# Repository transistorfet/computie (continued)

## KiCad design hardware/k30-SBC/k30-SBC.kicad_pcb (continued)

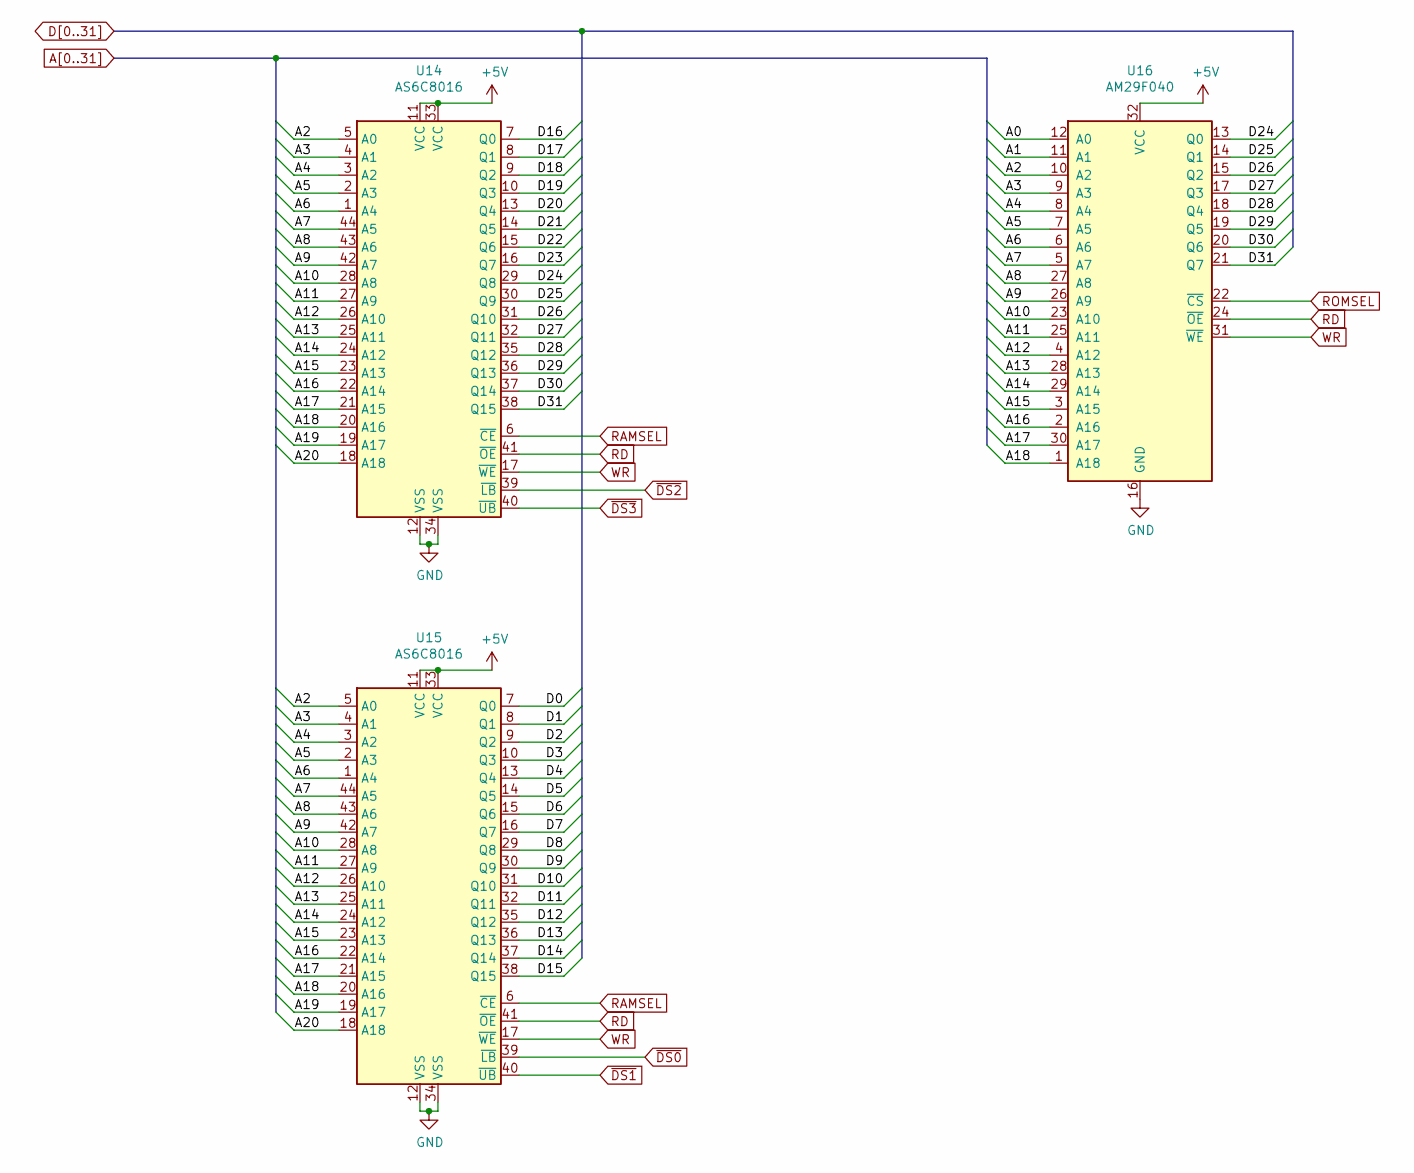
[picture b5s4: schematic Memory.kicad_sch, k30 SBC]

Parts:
U14, U15: AS6C8016; TSOP-II-44_10.16x18.41mm_P0.8mm
U16: AM29F040; PLCC-32_THT-Socket

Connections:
+5V: U14.11 (VCC), U14.33 (VCC), U15.11 (VCC), U15.33 (VCC), U16.32 (VCC); also elsewhere on the board
A0: U16.12 (A0); also elsewhere on the board
A1: U16.11 (A1); also elsewhere on the board
A2: U14.5 (A0), U15.5 (A0), U16.10 (A2); also elsewhere on the board
A3: U14.4 (A1), U15.4 (A1), U16.9 (A3); also elsewhere on the board
A4: U14.3 (A2), U15.3 (A2), U16.8 (A4); also elsewhere on the board
A5: U14.2 (A3), U15.2 (A3), U16.7 (A5); also elsewhere on the board
A6: U14.1 (A4), U15.1 (A4), U16.6 (A6); also elsewhere on the board
A7: U14.44 (A5), U15.44 (A5), U16.5 (A7); also elsewhere on the board
A8: U14.43 (A6), U15.43 (A6), U16.27 (A8); also elsewhere on the board
A9: U14.42 (A7), U15.42 (A7), U16.26 (A9); also elsewhere on the board
A10: U14.28 (A8), U15.28 (A8), U16.23 (A10); also elsewhere on the board
A11: U14.27 (A9), U15.27 (A9), U16.25 (A11); also elsewhere on the board
A12: U14.26 (A10), U15.26 (A10), U16.4 (A12); also elsewhere on the board
A13: U14.25 (A11), U15.25 (A11), U16.28 (A13); also elsewhere on the board
A14: U14.24 (A12), U15.24 (A12), U16.29 (A14); also elsewhere on the board
A15: U14.23 (A13), U15.23 (A13), U16.3 (A15); also elsewhere on the board
A16: U14.22 (A14), U15.22 (A14), U16.2 (A16); also elsewhere on the board
A17: U14.21 (A15), U15.21 (A15), U16.30 (A17); also elsewhere on the board
A18: U14.20 (A16), U15.20 (A16), U16.1 (A18); also elsewhere on the board
A19: U14.19 (A17), U15.19 (A17); also elsewhere on the board
A20: U14.18 (A18), U15.18 (A18); also elsewhere on the board
D0: U15.7 (Q0); also elsewhere on the board
D1: U15.8 (Q1); also elsewhere on the board
D2: U15.9 (Q2); also elsewhere on the board
D3: U15.10 (Q3); also elsewhere on the board
D4: U15.13 (Q4); also elsewhere on the board
D5: U15.14 (Q5); also elsewhere on the board
D6: U15.15 (Q6); also elsewhere on the board
D7: U15.16 (Q7); also elsewhere on the board
D8: U15.29 (Q8); also elsewhere on the board
D9: U15.30 (Q9); also elsewhere on the board
D10: U15.31 (Q10); also elsewhere on the board
D11: U15.32 (Q11); also elsewhere on the board
D12: U15.35 (Q12); also elsewhere on the board
D13: U15.36 (Q13); also elsewhere on the board
D14: U15.37 (Q14); also elsewhere on the board
D15: U15.38 (Q15); also elsewhere on the board
D16: U14.7 (Q0); also elsewhere on the board
D17: U14.8 (Q1); also elsewhere on the board
D18: U14.9 (Q2); also elsewhere on the board
D19: U14.10 (Q3); also elsewhere on the board
D20: U14.13 (Q4); also elsewhere on the board
D21: U14.14 (Q5); also elsewhere on the board
D22: U14.15 (Q6); also elsewhere on the board
D23: U14.16 (Q7); also elsewhere on the board
D24: U14.29 (Q8), U16.13 (Q0); also elsewhere on the board
D25: U14.30 (Q9), U16.14 (Q1); also elsewhere on the board
D26: U14.31 (Q10), U16.15 (Q2); also elsewhere on the board
D27: U14.32 (Q11), U16.17 (Q3); also elsewhere on the board
D28: U14.35 (Q12), U16.18 (Q4); also elsewhere on the board
D29: U14.36 (Q13), U16.19 (Q5); also elsewhere on the board
D30: U14.37 (Q14), U16.20 (Q6); also elsewhere on the board
D31: U14.38 (Q15), U16.21 (Q7); also elsewhere on the board
GND: U14.12 (VSS), U14.34 (VSS), U15.12 (VSS), U15.34 (VSS), U16.16 (GND); also elsewhere on the board
RAMSEL: U14.6 (~CE), U15.6 (~CE); also elsewhere on the board
RD: U14.41 (~OE), U15.41 (~OE), U16.24 (~OE); also elsewhere on the board
ROMSEL: U16.22 (~CS); also elsewhere on the board
WR: U14.17 (~WE), U15.17 (~WE), U16.31 (~WE); also elsewhere on the board
~DS0: U15.39 (~LB); also elsewhere on the board
~DS1: U15.40 (~UB); also elsewhere on the board
~DS2: U14.39 (~LB); also elsewhere on the board
~DS3: U14.40 (~UB); also elsewhere on the board

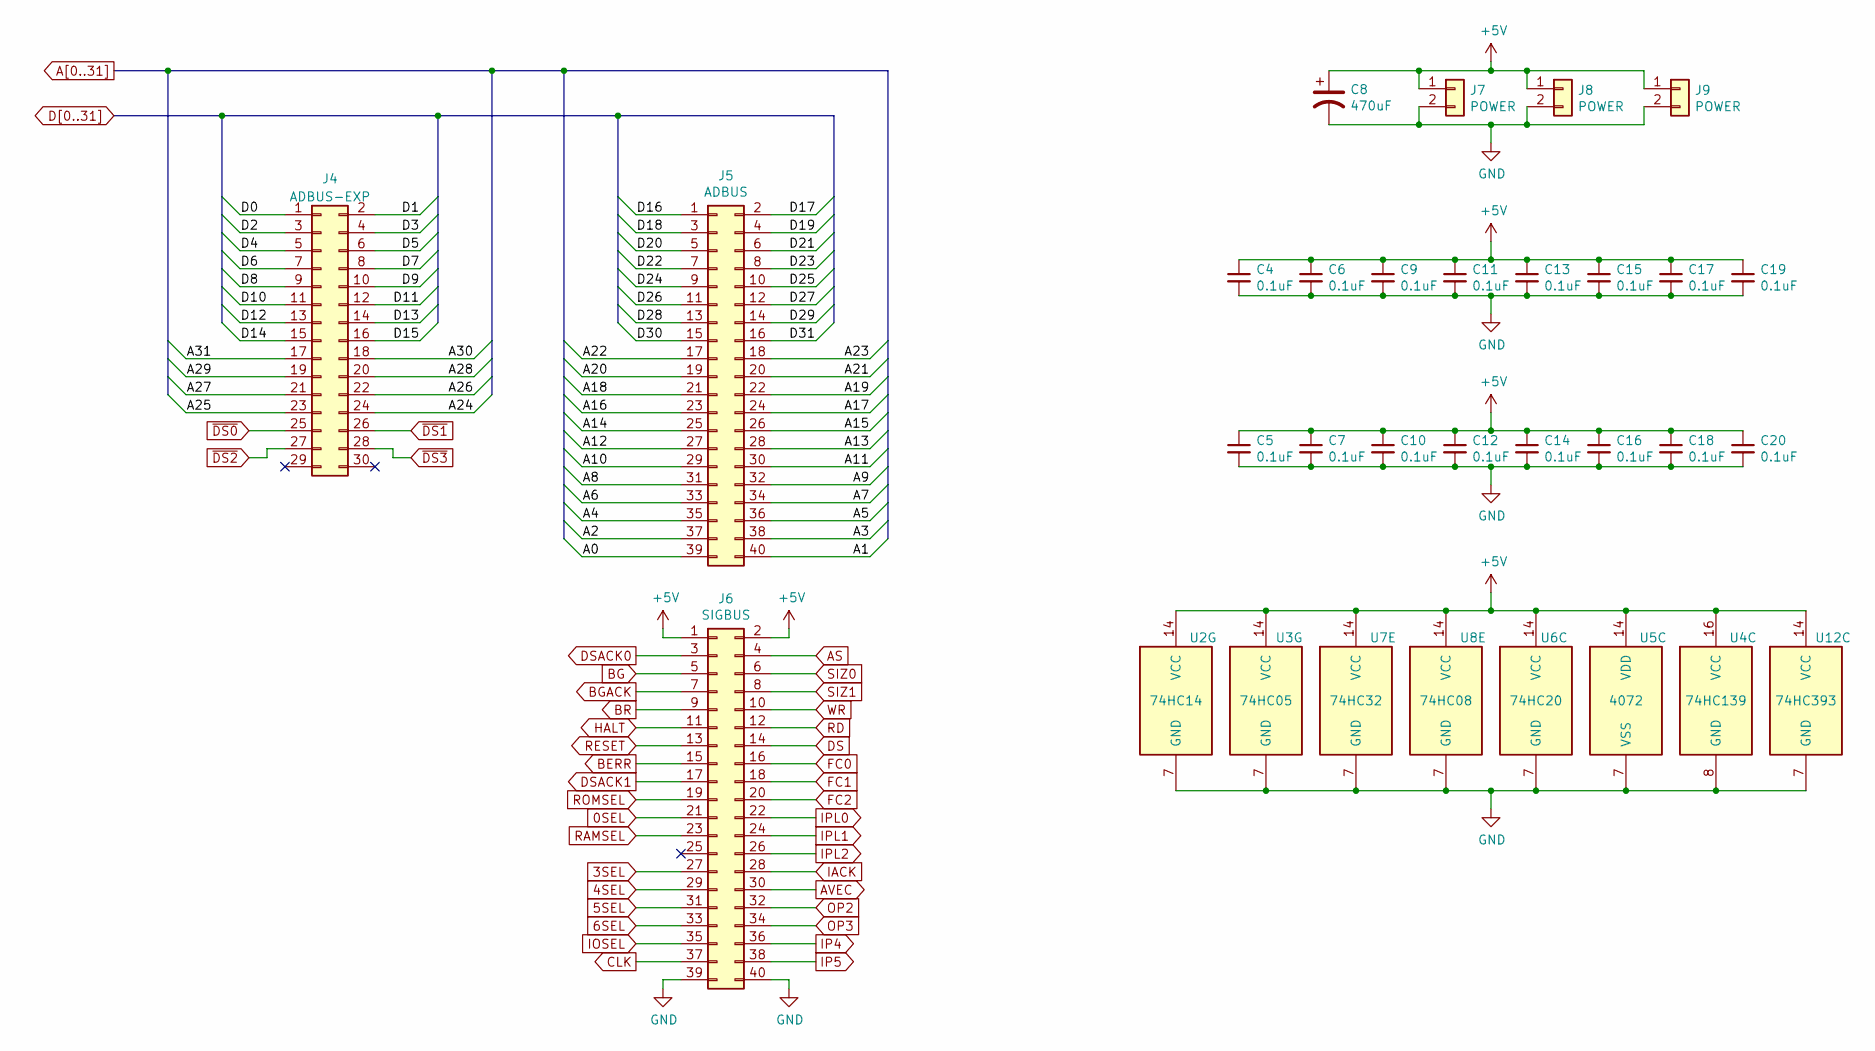
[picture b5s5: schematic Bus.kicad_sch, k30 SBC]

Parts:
C4, C5, C6, C7, C9, C10, C11, C12, C13, C14, C15, C16, C17, C18, C19, C20: 0.1uF; C_Disc_D3.0mm_W2.0mm_P2.50mm
C8: 470uF; CP_Radial_D8.0mm_P5.00mm
J4: ADBUS-EXP; PinHeader_2x15_P2.54mm_Vertical
J5: ADBUS; PinHeader_2x20_P2.54mm_Vertical
J6: SIGBUS; PinHeader_2x20_P2.54mm_Vertical
J7, J8, J9: POWER; PinHeader_1x02_P2.54mm_Vertical
U2: 74HC14; TSSOP-14_4.4x5mm_P0.65mm
U3: 74HC05; TSSOP-14_4.4x5mm_P0.65mm
U4: 74HC139; TSSOP-16_4.4x5mm_P0.65mm
U5: 4072; TSSOP-14_4.4x5mm_P0.65mm
U6: 74HC20; TSSOP-14_4.4x5mm_P0.65mm
U7: 74HC32; TSSOP-14_4.4x5mm_P0.65mm
U8: 74HC08; TSSOP-14_4.4x5mm_P0.65mm
U12: 74HC393; TSSOP-14_4.4x5mm_P0.65mm

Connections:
0SEL: J6.21; also elsewhere on the board
3SEL: J6.27; also elsewhere on the board
4SEL: J6.29; also elsewhere on the board
5SEL: J6.31; also elsewhere on the board
6SEL: J6.33; also elsewhere on the board
+5V: C4.1, C5.1, C6.1, C7.1, C8.1, C9.1, C10.1, C11.1, C12.1, C13.1, C14.1, C15.1, C16.1, C17.1, C18.1, C19.1, C20.1, J6.1, J6.2, J7.1, J8.1, J9.1, U2.14 (VCC), U3.14 (VCC), U4.16 (VCC), U5.14 (VDD), U6.14 (VCC), U7.14 (VCC), U8.14 (VCC), U12.14 (VCC); also elsewhere on the board
A0: J5.39; also elsewhere on the board
A1: J5.40; also elsewhere on the board
A2: J5.37; also elsewhere on the board
A3: J5.38; also elsewhere on the board
A4: J5.35; also elsewhere on the board
A5: J5.36; also elsewhere on the board
A6: J5.33; also elsewhere on the board
A7: J5.34; also elsewhere on the board
A8: J5.31; also elsewhere on the board
A9: J5.32; also elsewhere on the board
A10: J5.29; also elsewhere on the board
A11: J5.30; also elsewhere on the board
A12: J5.27; also elsewhere on the board
A13: J5.28; also elsewhere on the board
A14: J5.25; also elsewhere on the board
A15: J5.26; also elsewhere on the board
A16: J5.23; also elsewhere on the board
A17: J5.24; also elsewhere on the board
A18: J5.21; also elsewhere on the board
A19: J5.22; also elsewhere on the board
A20: J5.19; also elsewhere on the board
A21: J5.20; also elsewhere on the board
A22: J5.17; also elsewhere on the board
A23: J5.18; also elsewhere on the board
A24: J4.24; also elsewhere on the board
A25: J4.23; also elsewhere on the board
A26: J4.22; also elsewhere on the board
A27: J4.21; also elsewhere on the board
A28: J4.20; also elsewhere on the board
A29: J4.19; also elsewhere on the board
A30: J4.18; also elsewhere on the board
A31: J4.17; also elsewhere on the board
AS: J6.4; also elsewhere on the board
AVEC: J6.30; also elsewhere on the board
BERR: J6.15; also elsewhere on the board
BG: J6.5; also elsewhere on the board
BGACK: J6.7; also elsewhere on the board
BR: J6.9; also elsewhere on the board
CLK: J6.37; also elsewhere on the board
D0: J4.1; also elsewhere on the board
D1: J4.2; also elsewhere on the board
D2: J4.3; also elsewhere on the board
D3: J4.4; also elsewhere on the board
D4: J4.5; also elsewhere on the board
D5: J4.6; also elsewhere on the board
D6: J4.7; also elsewhere on the board
D7: J4.8; also elsewhere on the board
D8: J4.9; also elsewhere on the board
D9: J4.10; also elsewhere on the board
D10: J4.11; also elsewhere on the board
D11: J4.12; also elsewhere on the board
D12: J4.13; also elsewhere on the board
D13: J4.14; also elsewhere on the board
D14: J4.15; also elsewhere on the board
D15: J4.16; also elsewhere on the board
D16: J5.1; also elsewhere on the board
D17: J5.2; also elsewhere on the board
D18: J5.3; also elsewhere on the board
D19: J5.4; also elsewhere on the board
D20: J5.5; also elsewhere on the board
D21: J5.6; also elsewhere on the board
D22: J5.7; also elsewhere on the board
D23: J5.8; also elsewhere on the board
D24: J5.9; also elsewhere on the board
D25: J5.10; also elsewhere on the board
D26: J5.11; also elsewhere on the board
D27: J5.12; also elsewhere on the board
D28: J5.13; also elsewhere on the board
D29: J5.14; also elsewhere on the board
D30: J5.15; also elsewhere on the board
D31: J5.16; also elsewhere on the board
DS: J6.14; also elsewhere on the board
DSACK0: J6.3; also elsewhere on the board
DSACK1: J6.17; also elsewhere on the board
FC0: J6.16; also elsewhere on the board
FC1: J6.18; also elsewhere on the board
FC2: J6.20; also elsewhere on the board
GND: C4.2, C5.2, C6.2, C7.2, C8.2, C9.2, C10.2, C11.2, C12.2, C13.2, C14.2, C15.2, C16.2, C17.2, C18.2, C19.2, C20.2, J6.39, J6.40, J7.2, J8.2, J9.2, U2.7 (GND), U3.7 (GND), U4.8 (GND), U5.7 (VSS), U6.7 (GND), U7.7 (GND), U8.7 (GND), U12.7 (GND); also elsewhere on the board
HALT: J6.11; also elsewhere on the board
IACK: J6.28; also elsewhere on the board
IOSEL: J6.35; also elsewhere on the board
IP4: J6.36; also elsewhere on the board
IP5: J6.38; also elsewhere on the board
IPL0: J6.22; also elsewhere on the board
IPL1: J6.24; also elsewhere on the board
IPL2: J6.26; also elsewhere on the board
OP2: J6.32; also elsewhere on the board
OP3: J6.34; also elsewhere on the board
RAMSEL: J6.23; also elsewhere on the board
RD: J6.12; also elsewhere on the board
ROMSEL: J6.19; also elsewhere on the board
SIZ0: J6.6; also elsewhere on the board
SIZ1: J6.8; also elsewhere on the board
WR: J6.10; also elsewhere on the board
~DS0: J4.25; also elsewhere on the board
~DS1: J4.26; also elsewhere on the board
~DS2: J4.27; also elsewhere on the board
~DS3: J4.28; also elsewhere on the board

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
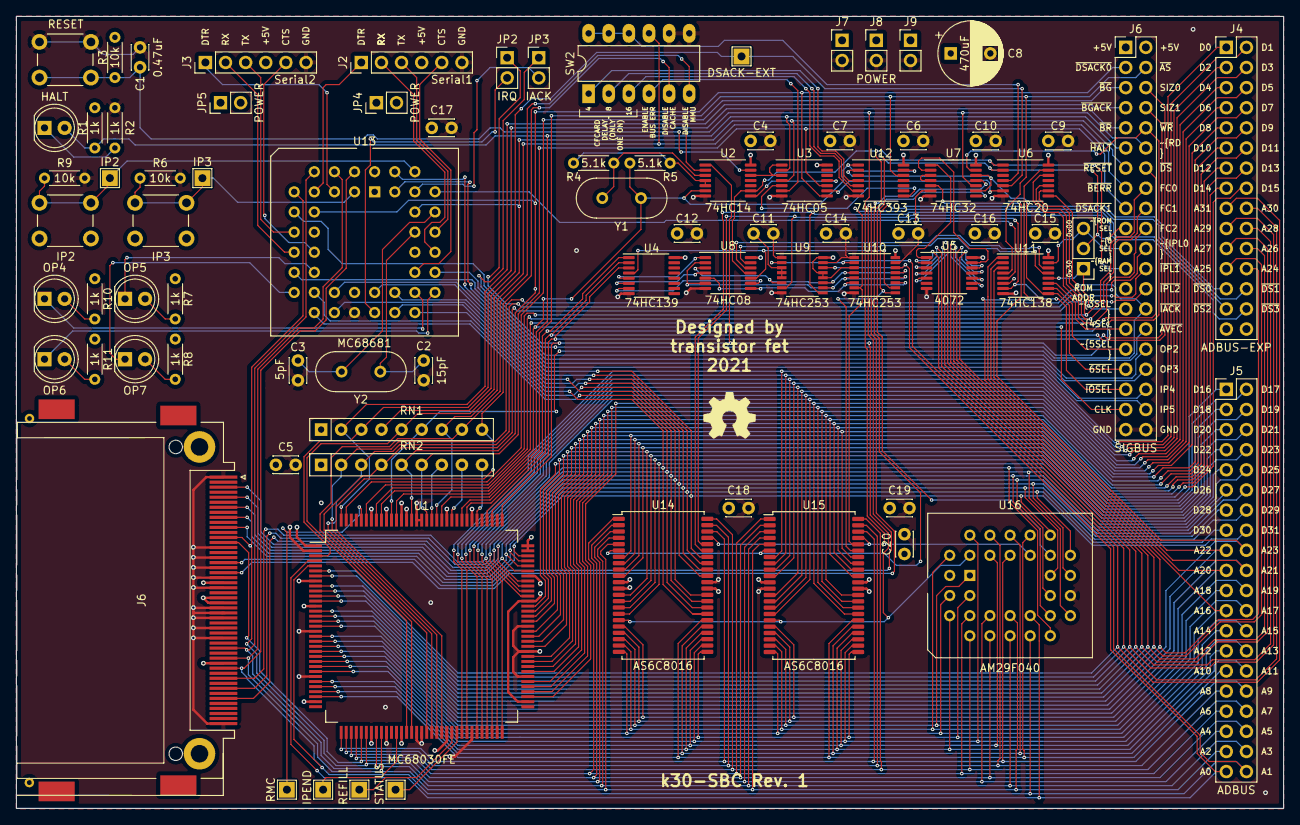
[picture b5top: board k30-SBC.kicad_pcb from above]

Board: 4 copper layers, 160.0 x 100.0 mm, 81 parts (0 on the bottom side), 167 nets.

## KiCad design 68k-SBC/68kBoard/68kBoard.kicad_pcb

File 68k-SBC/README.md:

The 68k Single Board Computer
=============================

A simple single board computer using a Motorola 68000 CPU, which can connect to a host computer via USB/TTL-Serial.
It has a bus for connecting a supervisor arduino or expansion devices, but it can operate standalone using the onboard
UARTs.  It has 64kB of onboard EEPROM, 1MB of onboard SRAM, and a 68681 Dual UART chip with GPIO.  Some of the GPIO
pins are wired to 4 general purpose LEDs and 2 general purpose buttons.

[68k Board Schematics](https://github.com/transistorfet/computie/raw/master/68k-SBC/68kBoard/68kBoard.pdf)

The serial ports require external TTL-to-something conversion and are designed to be used with an FTDI USB-to-Serial
cable or adapter.  Two optional jumpers can be used to supply power to the board from one of the USB ports (only one
should be jumped at a time, and only if the onboard power supply is disconnected), but it might be too much power to
source from USB, which is why it has the optional onboard power supply.

Two jumpers are provided to select what address the ROM will appear in (either 0x0000 or 0x2000), and whether to enable
onboard DTACK generation for address space 0x0000.  By moving the ROM to 0x2000 and disabling DTACK in 0x0000, a
connected arduino can boot the 68000 directly.

I decided to use discrete 74 Series chips for the glue logic to keep it simple and easy for others to build.  I tried
to minimize the amount of logic chips needed, so decided not to include interrupt support, which would have required at
least 2 more chips.  The interrupt acknowledge circuitry can be provided externally.

Breadboard Version
------------------

Revision 0
----------

I made a mistake and left out the logic for LDS/UDS in the chip select for the high and low memory chips.  When writing a
single byte to memory, it would also attempt to write to both the high and low chips, instead of only one.  Thanks to a poster
on EEVblog who suggested patching it with a P-channel MOSFET shown soldered to the back of the SRAM chips to interpose the UDS/LDS
signals into the chip selects, with the original traces cut.

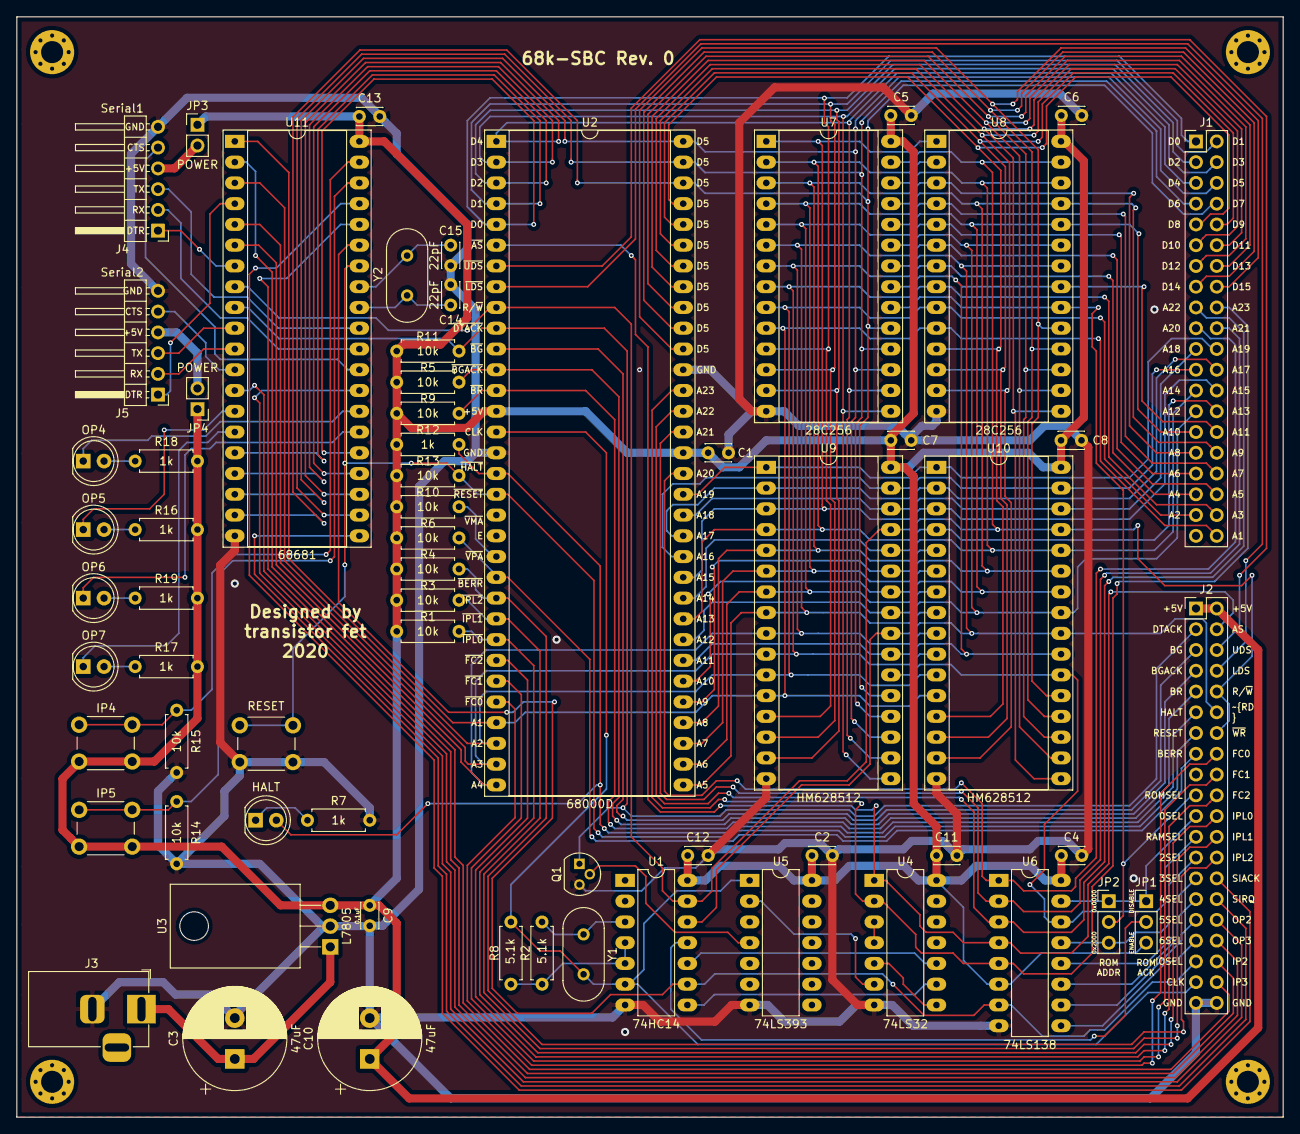
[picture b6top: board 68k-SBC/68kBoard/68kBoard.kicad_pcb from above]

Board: 2 copper layers, 154.9 x 134.6 mm, 65 parts (0 on the bottom side), 109 nets.

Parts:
C1, C2, C4, C5, C6, C7, C8, C9, C11, C12, C13: 0.1uF; C_Disc_D3.0mm_W2.0mm_P2.50mm
C3, C10: 47uF; CP_Radial_D12.5mm_P5.00mm
C14, C15: 22pF; C_Disc_D3.0mm_W2.0mm_P2.50mm
D1: HALT; LED_D5.0mm
D2: OP5; LED_D5.0mm
D3: OP7; LED_D5.0mm
D4: OP4; LED_D5.0mm
D5: OP6; LED_D5.0mm
J1: ADBUS; PinHeader_2x20_P2.54mm_Vertical
J2: SIGBUS; PinHeader_2x20_P2.54mm_Vertical
J3: Barrel_Jack; BarrelJack_Horizontal
J4: Serial1; PinHeader_1x06_P2.54mm_Horizontal
J5: Serial2; PinHeader_1x06_P2.54mm_Horizontal
JP1: ROMACK; PinHeader_1x03_P2.54mm_Vertical
JP2: ROMJMP; PinHeader_1x03_P2.54mm_Vertical
JP3, JP4: POWER; PinHeader_1x02_P2.54mm_Vertical
Q1: Q_NMOS_DGS; TO-92
R1, R3, R4, R5, R6, R9, R10, R11, R13, R14, R15: 10k; R_Axial_DIN0207_L6.3mm_D2.5mm_P7.62mm_Horizontal
R2, R8: 5.1k; R_Axial_DIN0207_L6.3mm_D2.5mm_P7.62mm_Horizontal
R7, R12, R16, R17, R18, R19: 1k; R_Axial_DIN0207_L6.3mm_D2.5mm_P7.62mm_Horizontal
SW1: RESET; SW_PUSH_6mm
SW2: IP4; SW_PUSH_6mm
SW3: IP5; SW_PUSH_6mm
U1: 74HC14; DIP-14_W7.62mm_LongPads
U2: 68000D; DIP-64_W22.86mm_Socket_LongPads
U3: L7805; TO-220-3_Horizontal_TabDown
U4: 74LS32; DIP-14_W7.62mm_LongPads
U5: 74LS393; DIP-14_W7.62mm_LongPads
U6: 74LS138; DIP-16_W7.62mm_LongPads
U7, U8: 28C256; DIP-28_W15.24mm_Socket_LongPads
U9, U10: HM628512; DIP-32_W15.24mm_Socket_LongPads
U11: 68681; DIP-40_W15.24mm_Socket_LongPads
Y1, Y2: Crystal; Crystal_HC49-4H_Vertical

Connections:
0SEL: J2.21, JP1.1, JP2.1, U6.15
2SEL: J2.25, JP2.3, U6.13
3SEL: J2.27, U6.12
4SEL: J2.29, U6.11
5SEL: J2.31, U6.10
6SEL: J2.33, U6.9
+5V: C1.1, C2.1, C4.1, C5.1, C6.1, C7.1, C8.1, C9.1, C10.1, C11.1, C12.1, C13.1, J2.1, J2.2, JP1.3, JP3.1, JP4.1, R1.1, R3.1, R4.1, R5.1, R6.1, R9.1, R10.1, R11.1, R12.1, R13.1, R16.2, R17.2, R18.2, R19.2, SW2.2, SW3.2, U1.14, U2.14, U2.49, U3.3, U4.14, U5.14, U6.6, U6.16, U7.28, U8.28, U9.32, U10.32, U11.40
A1: J1.40, U2.29, U7.10, U8.10, U9.12, U10.12, U11.1
A2: J1.37, U2.30, U7.9, U8.9, U9.11, U10.11, U11.3
A3: J1.38, U2.31, U7.8, U8.8, U9.10, U10.10, U11.5
A4: J1.35, U2.32, U7.7, U8.7, U9.9, U10.9, U11.6
A5: J1.36, U2.33, U7.6, U8.6, U9.8, U10.8
A6: J1.33, U2.34, U7.5, U8.5, U9.7, U10.7
A7: J1.34, U2.35, U7.4, U8.4, U9.6, U10.6
A8: J1.31, U2.36, U7.3, U8.3, U9.5, U10.5
A9: J1.32, U2.37, U7.25, U8.25, U9.27, U10.27
A10: J1.29, U2.38, U7.24, U8.24, U9.26, U10.26
A11: J1.30, U2.39, U7.21, U8.21, U9.23, U10.23
A12: J1.27, U2.40, U7.23, U8.23, U9.25, U10.25
A13: J1.28, U2.41, U7.2, U8.2, U9.4, U10.4
A14: J1.25, U2.42, U7.26, U8.26, U9.28, U10.28
A15: J1.26, U2.43, U7.1, U8.1, U9.3, U10.3
A16: J1.23, U2.44, U9.31, U10.31
A17: J1.24, U2.45, U9.2, U10.2
A18: J1.21, U2.46, U9.30, U10.30
A19: J1.22, U2.47, U9.1, U10.1
A20: J1.19, U2.48, U6.1
A21: J1.20, U2.50, U6.2
A22: J1.17, U2.51, U6.3
A23: J1.18, U2.52, U4.2, U6.5
AS: J2.4, U2.6, U4.1, U6.4
BERR: J2.15, R6.2, U2.22
BG: J2.5, U2.11
BGACK: J2.7, R5.2, U2.12
BR: J2.9, R9.2, U2.13
CLK: J2.37, R8.1, U1.6, U2.15, U5.1, Y1.2
D0: J1.1, U2.5, U7.11, U9.13, U11.25
D1: J1.2, U2.4, U7.12, U9.14, U11.16
D2: J1.3, U2.3, U7.13, U9.15, U11.24
D3: J1.4, U2.2, U7.15, U9.17, U11.17
D4: J1.5, U2.1, U7.16, U9.18, U11.23
D5: J1.6, U2.64, U7.17, U9.19, U11.18
D6: J1.7, U2.63, U7.18, U9.20, U11.22
D7: J1.8, U2.62, U7.19, U9.21, U11.19
D8: J1.9, U2.61, U8.11, U10.13
D9: J1.10, U2.60, U8.12, U10.14
D10: J1.11, U2.59, U8.13, U10.15
D11: J1.12, U2.58, U8.15, U10.17
D12: J1.13, U2.57, U8.16, U10.18
D13: J1.14, U2.56, U8.17, U10.19
D14: J1.15, U2.55, U8.18, U10.20
D15: J1.16, U2.54, U8.19, U10.21
DTACK: J2.3, Q1.1, R11.2, U2.10, U11.9
FC0: J2.16, U2.28
FC1: J2.18, U2.27
FC2: J2.20, U2.26
GND: C1.2, C2.2, C3.2, C4.2, C5.2, C6.2, C7.2, C8.2, C9.2, C10.2, C11.2, C12.2, C13.2, C14.1, C15.1, J2.39, J2.40, J3.2, J4.6, J5.6, Q1.3, R7.2, R14.2, R15.2, SW1.1, U1.7, U2.16, U2.53, U3.2, U4.7, U5.7, U6.8, U7.14, U8.14, U9.16, U10.16, U11.20
HALT: D1.2, J2.11, R12.2, U2.17
IOSEL: J2.35, U1.9, U6.7, U11.35
IP2: J2.36, U11.36
IP3: J2.38, U11.2
IPL0: J2.22, R1.2, U2.25
IPL1: J2.24, R3.2, U2.24
IPL2: J2.26, R4.2, U2.23
LDS: J2.8, U2.8
unnamed: C3.1, J3.1, U3.1
unnamed: C14.2, U11.32, Y2.2
unnamed: C15.2, U11.33, Y2.1
unnamed: D1.1, R7.1
unnamed: D2.1, U11.14
unnamed: D2.2, R16.1
unnamed: D3.1, U11.15
unnamed: D3.2, R17.1
unnamed: D4.1, U11.27
unnamed: D4.2, R18.1
unnamed: D5.1, U11.26
unnamed: D5.2, R19.1
unnamed: J4.1, U11.7
unnamed: J4.2, U11.30
unnamed: J4.3, U11.31
unnamed: J4.4, JP3.2
unnamed: J4.5, U11.29
unnamed: J5.1, U11.4
unnamed: J5.2, U11.11
unnamed: J5.3, U11.10
unnamed: J5.4, JP4.2
unnamed: J5.5, U11.12
unnamed: JP1.2, U1.11
unnamed: Q1.2, U5.4
unnamed: R2.1, R8.2, U1.4, U1.5
unnamed: R2.2, U1.3, Y1.1
unnamed: R10.2, U2.21
unnamed: R14.1, SW3.1, U11.38
unnamed: R15.1, SW2.1, U11.39
unnamed: U1.8, U4.9
unnamed: U1.10, U4.10
unnamed: U4.3, U4.4
unnamed: U4.5, U4.8
unnamed: U4.6, U5.2
OP2: J2.32, U11.28
OP3: J2.34, U11.13
RAMSEL: J2.23, U6.14, U9.22, U10.22
RD: J2.12, U1.12, U7.22, U8.22, U9.24, U10.24
RESET: J2.13, R13.2, SW1.2, U2.18, U11.34
ROMSEL: J2.19, JP2.2, U7.20, U8.20
R~W: J2.10, J2.14, U1.13, U2.9, U7.27, U8.27, U9.29, U10.29, U11.8
SIACK: J2.28, U11.37
SIRQ: J2.30, U11.21
UDS: J2.6, U2.7

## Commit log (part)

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2019-11-24 Modified to allow serial input to the Z80 program
2019-12-03 Added readme for 68k SBC
2019-12-20 Changed to png schematic
2019-12-26 Factored out libc, compiled to .a, with a file for each function
2020-03-01 Added images for Z80-NQC
2020-03-01 Updated root readme
2020-03-27 Reordered address and data buses for easier connection to arduino
2020-03-28 Finalized 68kBoard and 68kBoardSupervisorShield
2020-04-17 Added 68kBoard rev.0 zip and errata
2020-05-23 Added images
2020-05-23 Modified build system to use a linker script
2020-05-26 Resized image
2020-05-28 Added simple heap allocator
2020-06-11 Fixed issue preventing optimizated output from running correctly
2020-06-13 Separated hardware and software files
2020-06-14 Got system calls working more cleanly
2020-06-17 Added 68681 timer interrupt and fixed exception error printing
2020-06-23 Got context switching working
2020-06-25 More clean up
2020-06-27 Added the exit syscall, and insert it after main returns
2020-06-29 Fork syscall is now working, more or less
2020-07-02 Modified monitor fatal errors interrupt
2020-07-06 Added mallocfs (simple malloc-backed fs with a fixed block size)
2020-07-07 Added stat() and syscall stubs
2020-07-08 Suspending processes when no input is available is partially working
2020-07-10 Fixed tty buffer issues, added some flow control (but not perfect yet), and started implementing unlink
2020-07-11 Added wait syscall, and improved mallocfs's seek function
2020-07-11 Added . and .. entries to mallocfs
2020-07-13 Added missing buffer definition file
2020-07-18 Added pipes and printk
2020-07-19 Added arguments to exec, copied to the new process's stack
2020-07-23 Reorganized to separate hardware and software at the top level
2020-08-17 Final version of rev 2
2020-08-18 Removed vnode and moved allocation to filesystems
2020-08-20 Moved printk.h into include/
2020-08-21 Added O_TRUNC and a few fixes
2020-08-22 Regularized the pseudo commands in sh.c
2020-08-23 Added proper bitmap init function
2020-08-27 Minor changes
2020-08-30 Resize image
2020-09-03 Added mode arg to open() and fixed a scheduling bug
2020-09-03 Modified file refcounting
2020-09-05 Added current working directory to process struct, and chdir()
2020-09-06 Added file renaming to vfs/mallocfs
2020-09-12 Partially added command redirecting, added dup2() syscall, and fixed issue where printf was using direct output
2020-09-14 Fixed double free bug, and added a double free check to stdlib
2020-09-15 Added the start of mounting
2020-09-18 Removed mallocfs-unique zone type
2020-09-19 Initial implementation of minixfs
2020-09-20 Added preinit for serial console such that the buffer is saved and printed when interrupts are enabled
2020-09-21 Moved access module to fs/
2020-09-21 Fixed issue with chdir
2020-09-22 Refactored exec/process code (partially)
2020-09-23 Refactored mkfs a bit
2020-09-23 Added uid to create/mknod vfs calls
2020-09-24 Added mem driver, and modified bufcache to use drivers with a given offset
2020-09-25 Increased the data returned by stat() and stored in the vnode
2020-09-26 Changed some values back after testing zone trees
2020-09-27 Modified command executor to check for a file before checking the builtin commands
2020-09-27 Moved tests to init for now, so that sh has no kernel calls
2020-09-28 Fixed time() argument
2020-09-29 Added mount/umount syscall
2020-09-30 Added kill and sync syscalls, but signals are not yet implemented
2020-10-08 Fixed signal mask code
2020-10-09 Added sending signals to process groups
2020-10-15 Refactored to use vfile ops for device access for device special files
2020-10-15 Added argument to new_proc to specify an exact pid to use, or 0 for the next one
2020-10-18 Reorganized kicad files
2020-10-22 Removed the use of current_proc_stack by directly using current_proc
2020-11-05 Added procfs and fixed a refcount bug with mounted filesystems
2020-11-05 Added kill command
2020-11-27 Added 68k-SMT board, which is similar to 68k-SBC, but with PLCC/SMT components and a CompactFlash card slot
2020-11-30 Added little-endian support for minix to be interoperable with other minixfs implementations
2020-12-01 Finalized 68k-SMT board and sent off to print
2020-12-04 Changed unlink to take the filename
2020-12-06 Fixed minix vnode cache
2020-12-07 Improved echo command and moved sync into its own command
2020-12-07 Added extra checks to vfs_link() and fixed a bug in echo
2020-12-07 Added ata detection code
2020-12-14 Added a verify command to the supervisor
2020-12-14 Removed debug prints and fixed flat binary execution as a fallback
2020-12-16 Fixed some compiler warnings
2020-12-17 Fixed LOCK/UNLOCK to not generate code using the address registers
2020-12-19 Removed some unused test code
2020-12-20 Added environment variables and env expansion in 'echo'
2020-12-23 Fixed flow control in the interrupt-driven serial driver, and optimized a bit
2020-12-26 Added strncmp and strcat to libc
2020-12-26 Added simple tar command (extraction only, no flags)
2020-12-28 Fixed echoing in monitor, and added help and erase commands
    It's now possible to use the load command to load the latest copy of
    the monitor rom into ram over serial, and then eraserom and writerom
    to burn the new copy of the monitor into flash
2020-12-28 Added arguments for loading binaries
2020-12-30 Added a primative bootloader, which can load the kernel from disk
2020-12-30 Fixed bug when cloning cmdline args during fork
2021-01-02 Refactored functions for creating new process memory during exec/clone
2021-01-06 Added some termios functions
2021-01-07 Modified signals to support the SA_RESTART flag, or cancel the syscall in progress otherwise
2021-01-08 Fixed some compiler errors/warnings when compiling commands individually
2021-01-08 Added a description for the video in the readme
2021-01-08 Added parsing of double quotes in command line
2021-01-08 Added rdev to stat() and display it in ls command
2021-01-09 Added sscanf implementation, and use it in the ps command
2021-01-10 Updated todo
2021-01-10 Added more formats to strftime() and fixed a bug with file redirection
2021-01-10 Updated OS demo gif
2021-01-11 Added strncat()
2021-01-12 Added device file creation to the makefile
2021-01-12 Reset tty input buffer on ^C and added some delays to fix garbled output
2021-01-12 Added addr arguments to eraserom, writerom, verifyrom in monitor
2021-01-12 Moved procfs data functions into their own file
2021-01-16 Fixed odd size issue with load and send commands
2021-01-18 Minor refactoring and fixed some compiler warnings
2021-01-22 Improved handling of user vs fatal exceptions
2021-01-23 Fixed elf loading bug and added relocation
    The previous elf loader was only loading one segment instead of all program
    header load segments, which was causing the process segment to be way too
    small, pushing the bss out into neighbouring memory. I believe this was
    causing the issue where the command list data was overwriting the text
    segment causing a catastrophic failure.
    I also fixed an issue where a process could fail after modifying the memory
2021-01-24 Renamed SH_ to BH_ in the bottom half code to be consistent
2021-01-27 Modified file mode checks to use stat.h macros
2021-02-02 Added initial networking module
    This is the initial commit of the networking subsystem that I've been
    working on for the past two weeks. It supports very simple UDP messages
    without checksum calculations or address processing, and is able to
    receive UDP messages sent from the host computer. Sending shows the
    packets in wireshark, but receiving on the host is not quite working.
    I wanted to get the partial work committed before making changes to
2021-02-03 Added simple ping response and added ns command
    The implementation of ICMP is hacky and I'll need to change the
    header encoding and packet creation functions somehow to make it
    cleaner.
    I also added a simple UDP sending program, ns. It will eventually
    take an ip and port number but for now, they are hardcoded
2021-02-03 Moved packet creation to be within the protocol implementations
2021-02-04 Added port argument to ns command
2021-02-04 Fixed bug in procfs where extra files not listed
    Only the process directories were being returned by readdir() and
    not the /proc/mounts file. There is now a different way of using
    file->position to represent the position of either the process_iter
    or the current static root file slot
2021-02-04 Added getopt() function and used in mount command
2021-02-05 Fixed issue with gap between the text and data segments
2021-02-06 Fixed network forwarding issue on linux
2021-02-06 Added ntpdate command to set the timestamp
2021-02-07 Added inode field to the vnode struct
2021-02-07 Fixed issues with mounted fs in lookup and reverse lookup
2021-02-09 Added simple ifconfig command, and added uid to all ioctl functions
2021-02-10 Fixed bug in ipv4 checksum for odd-length packets
2021-02-10 Added os-specific malloc that uses sbrk()
2021-02-11 Added rand() and used in epdemeral port assignment
2021-02-13 Added simple TCP implementation
    There are no timers, retries, or reordering of packets, but it can
    connect and transmit data in either direction
2021-02-14 Refactored the protocol implementations
2021-02-15 Moved process syscalls to the top, to match api.h
2021-02-15 Minor timing fixes to the monitor after swapping the crystal
2021-02-16 Added fprintf, fscanf, fread, fwrite, and other libc functions
2021-02-18 Rewrote ns command to do client/server tcp/udp
    And fixed a problem with sendto/recvfrom where the const void *
    options weren't compiling correctly, but they've been changed to int
2021-02-18 Removed unused code from the GNU elf.h include
2021-02-19 Added buffering to libc reading (but not writing)
2021-02-20 Added file argument to sh, and exec /etc/rc by init
2021-02-20 Missed the new files
2021-02-21 Fixed boot loader to run from rom
    Only the stack variables are mutable, since any static variables
    in rom can't be written to
2021-02-21 Modified to allow kernel to run /bin/init directly
2021-02-22 Re-wrote timer.c to use a list of timers with callbacks
2021-02-24 Added select() syscall
    This required modifying the wait checking to allow custom wait functions
    and adding a vfs file operation, poll, which can return whether a file
    or device or endpoint is ready for reading/writing.
2021-02-25 Converted syscall numbers in suspend/resume to poll flags
2021-02-25 Added checks for MC68681 errors
2021-02-25 Fixed issue with backspace in tty
2021-02-26 Added simple response to simple http server
2021-03-01 Fixed bug causing hang at boot
2021-03-02 Added missing support for stdin redirect in sh
2021-03-13 Testing relative markdown links
2021-09-04 Added MemTest and FlashTest arduino programs
2021-09-09 Fixed image links
2021-10-03 Changed monitor.ld so the elf and bin have the same addresses
2021-11-28 Renamed images for posts
2021-11-28 Almost completed k30-SBC board design
2021-12-05 Last minute changes: swapped WR/DS pins, added testpoint
2021-12-06 Final k30-SBC rev1 design, sent to production
2022-02-11 Updated errata for k30
2022-10-31 Revision 2 for k30-SBC minus a few fixes
2022-10-31 Upgraded project formats to kicad 6.0
2022-11-14 Revision 2 of k30-SBC
2022-12-21 Fixed issue caused by optimizations in strlen
2023-04-08 Added software compiling and flashing instructions
2023-05-29 Modified command parsing to match monitor, c/w help command
2023-07-07 Identified issue with pull up resistor size for DSACK
    Also included an improvement of the fatal error message in the monitor
2023-08-08 Moved the OS, now called gloworm, into its own directory
2024-08-08 Added images to board readme
